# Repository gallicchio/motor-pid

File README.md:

# PID Motor Control Loop PCB

The motor-position feedback loop of *Learning the Art of Electronics* (Hayes &
Horowitz), Lab 10L, as a 170 x 120 mm printed circuit board whose silkscreen *is*
the schematic.  A motorized slide fader (the lab's Bourns PSM01-082A-103B2, or
any 100 mm fader with a 10k track and a 6–11 V motor) wires to two screw terminals; the
board holds the fader's wiper at the position a knob or a signal generator asks
for, with proportional, derivative and integral terms the student switches in
and turns up one at a time, exactly as the lab does.

Every node the lab asks you to look at has a probe loop (17 probe loops, four
of them ground).  Every stage sits in a dashed box named as the book names it.
The three gain trimmers are labelled P GAIN, D GAIN and I GAIN, each with an arc
over it saying what clockwise does (more resistance: more P, more D, less I);
the switches say in words what each position does.

## What is on it

| block | the book | here |
|---|---|---|
| TARGET | a 10k pot between ±15 V through 6.8k | a knob with a centre detent (0 V, clockwise positive), or a BNC jack for a slow square wave; a switch picks |
| pseudo op-amp | unity difference amplifier, inverter, summing amplifier | U1, U2, U3 (LM321) with 100k and 10k as drawn; the summing amplifier's gain is the P GAIN trimmer |
| derivative | C and 1k into an op-amp with 1M feedback, 470 pF across it | U4; a switch picks 22 nF (right for this fader) or the book's 100 nF; D IN / OFF switch |
| integral | 1k + 1M into an op-amp with a capacitor across it | U5 with a 1 µF polypropylene film (its value holds at any voltage); I IN / OFF, where OFF shorts the capacitor so the integrator starts from zero |
| motor driver | op-amp driving a push-pull pair, 10k feedback from the motor side, 0.33 µF from the op-amp's own output, 270 Ω into the bases, 10 Ω + 0.1 µF snubber | U6 with MJB44H11 / MJB45H11 in D2PAK, each in a 2 oz copper pour that is its heatsink, clamp diodes to the rails, a 0.35 A resettable fuse between the push-pull and DRIVE, with red lamps across it: the feedback, the DRIVE loop, DRIVE OUT and the motor are behind it; two more Schottkys clamp a rail left open |
| the plant | the fader's motor and 10k track with 4.7k end resistors (±7.7 V) | two 3-way screw terminals, MOTOR and POT, a POSITION probe loop and a buffered POSITION OUT jack |
| LOOP switch | the book's "break the loop here" | open (POSITION replaced by ground) or closed |

The design departs from the book where the parts or the pedagogy asked for it;
each departure is in [docs/DESIGN_NOTES.md](docs/DESIGN_NOTES.md).

## Using it

[docs/HANDBOOK.md](docs/HANDBOOK.md): bring-up without the fader, wiring the
fader and checking its polarity, the expected voltage at every loop, and the
lab's exercises in the lab's order (P alone and the residual error, raising the
gain until it oscillates, adding D, then I, then driving it with a square
wave).  The back of the board carries the short version.

## Ordering it

[docs/MANUFACTURING.md](docs/MANUFACTURING.md) is generated by the build: the
files to upload, JLCPCB's order form field by field, the cost, and what to look
at in their placement preview.  There are about $12.21 in parts per board.
Order **2 oz** outer copper, not the default 1 oz: the copper round the two
power transistors is their heatsink.

## Building it

```
./make.py
```

runs, from `scripts/parts.py` outward: the footprints and 3D stand-ins, the
ngspice simulation of the loop (from the exported netlist, with a model of the
fader), the schematic (`scripts/gen_sch.py`) and its ERC, 258 circuit
assertions on the netlist (`scripts/check_circuit.py`), the board
(`scripts/layout.py` placed and wired by `scripts/gen_pcb.py`, where every
drawn wire is laid as copper) and its DRC with schematic parity, the fab
package and its checks (`scripts/check_outputs.py`), and the documents, whose
every quoted number is checked against the build.  KiCad 10 is needed; the
build finds its AppImage.

## Files

- `hardware/` — the KiCad project (generated; do not edit by hand)
- `scripts/` — the generators and checkers
- `sim/` — the simulation and its results
- `out/motorpid/` — gerbers, BOM, CPL, prints, assembly notes
- `docs/` — handbook, design notes, manufacturing, images
- `CLAUDE_CODE_CHAT.md` — how this was designed, prompt by prompt

## Licence

Hardware under CERN-OHL-P v2 (`LICENSE-HARDWARE.txt`), scripts under MIT
(`LICENSE`).  The circuit is Hayes & Horowitz's; the board is Jason Gallicchio
and Claude, 2026.

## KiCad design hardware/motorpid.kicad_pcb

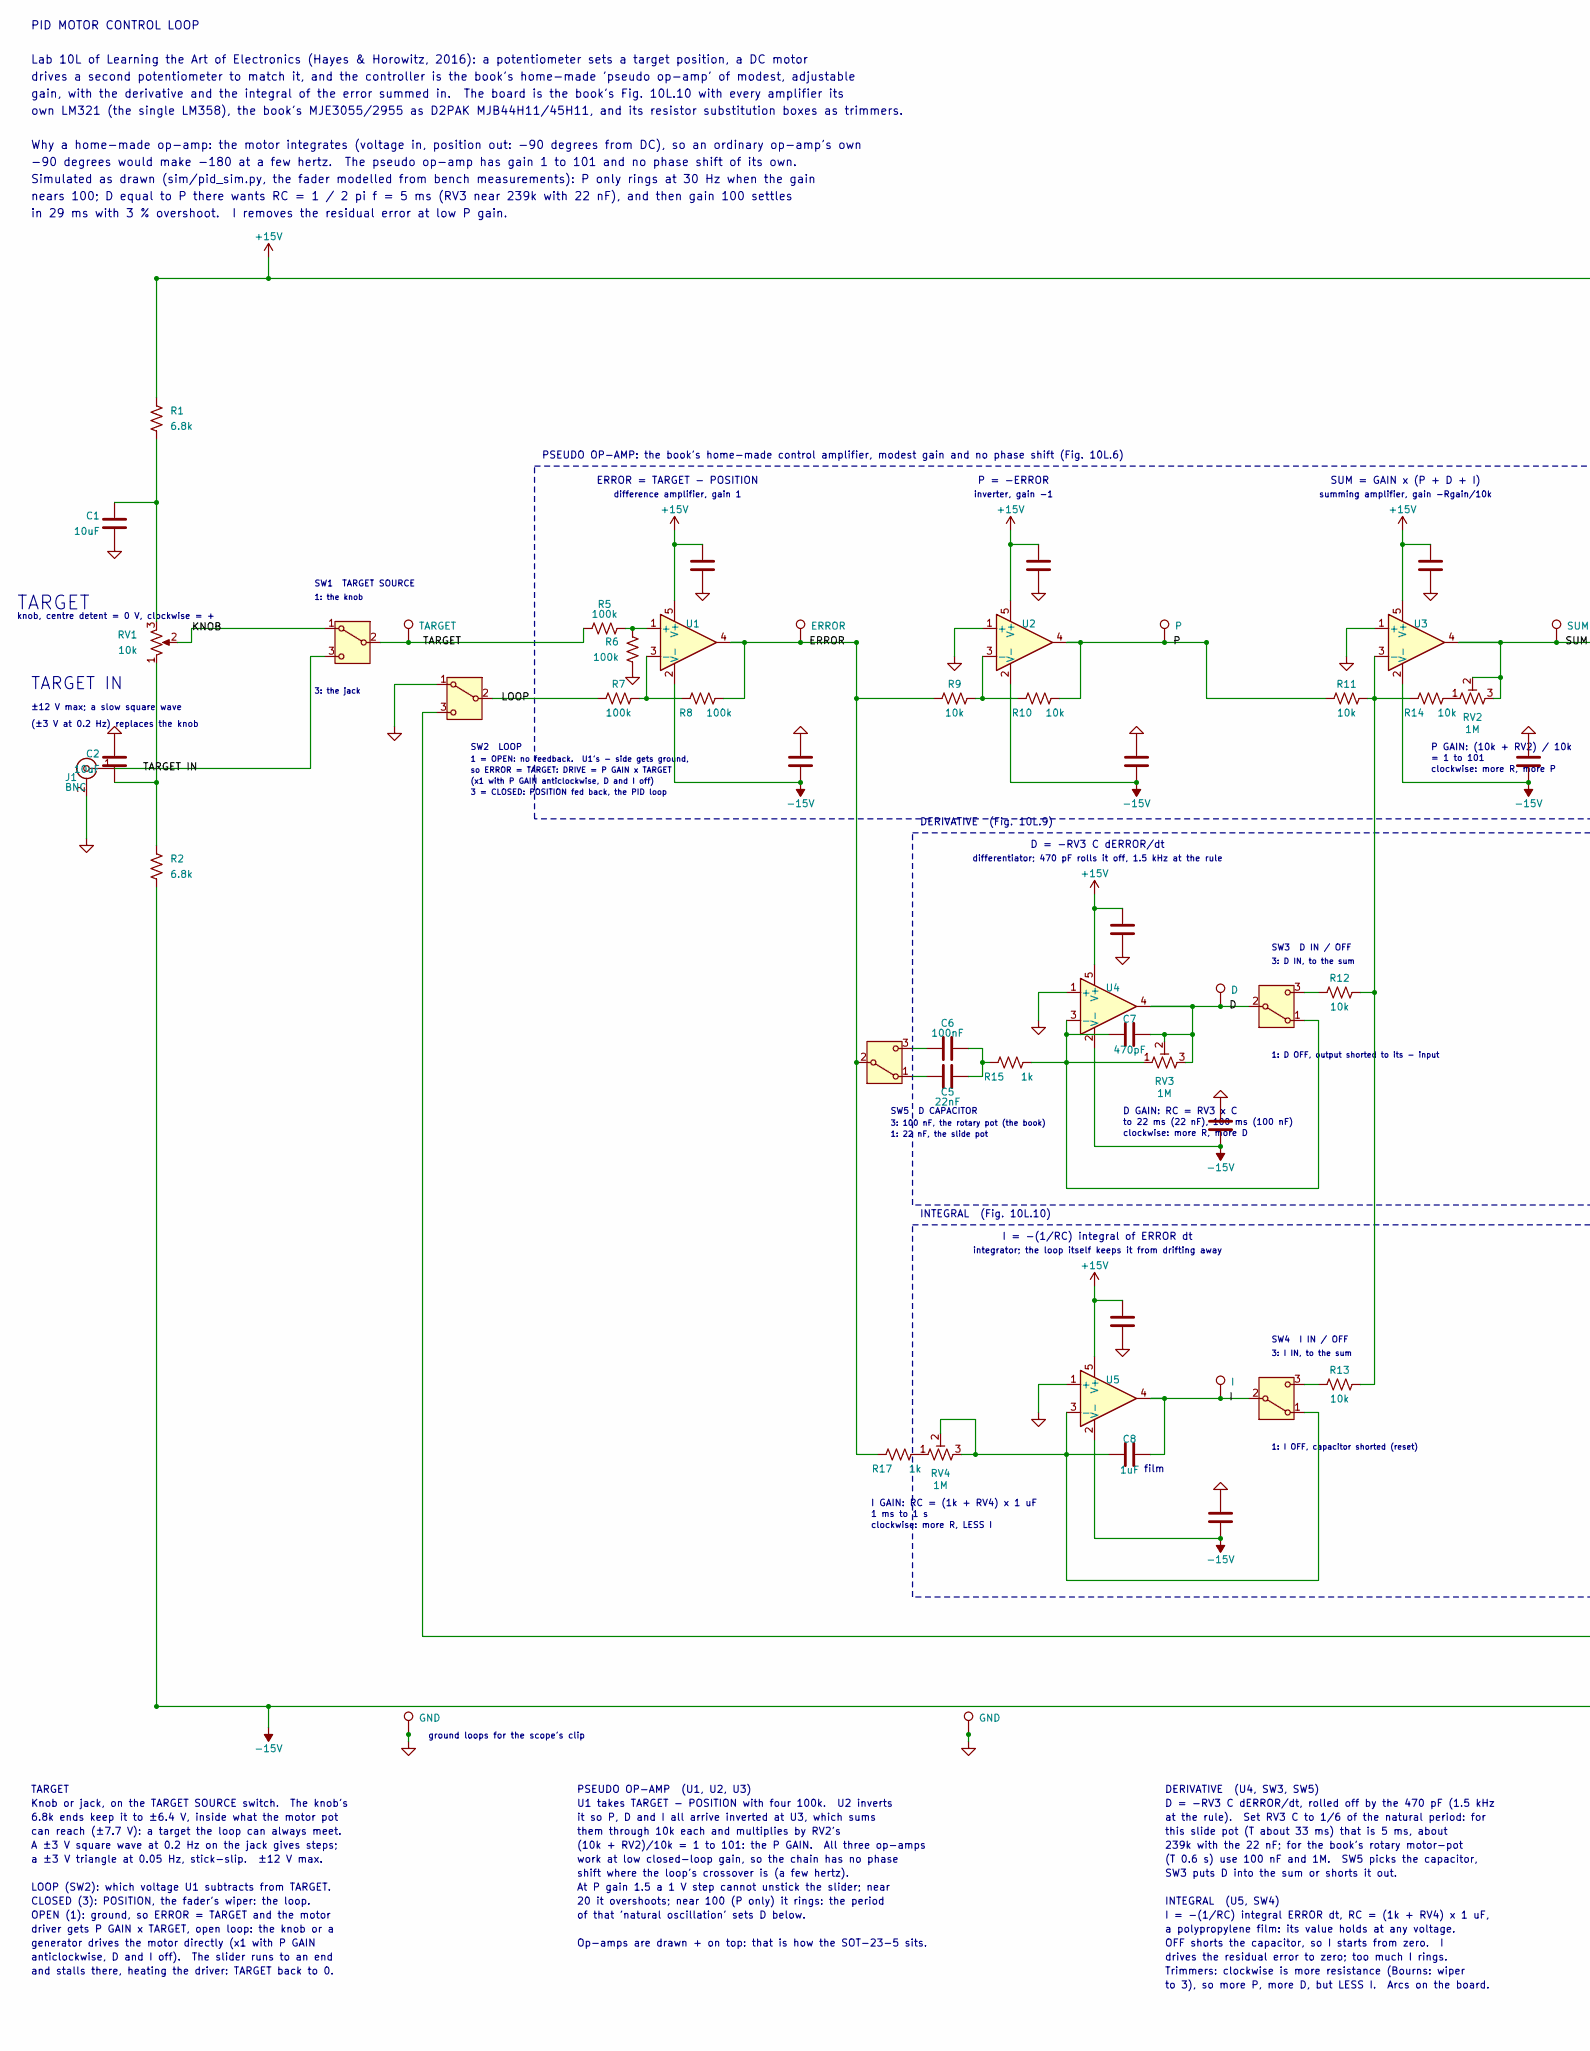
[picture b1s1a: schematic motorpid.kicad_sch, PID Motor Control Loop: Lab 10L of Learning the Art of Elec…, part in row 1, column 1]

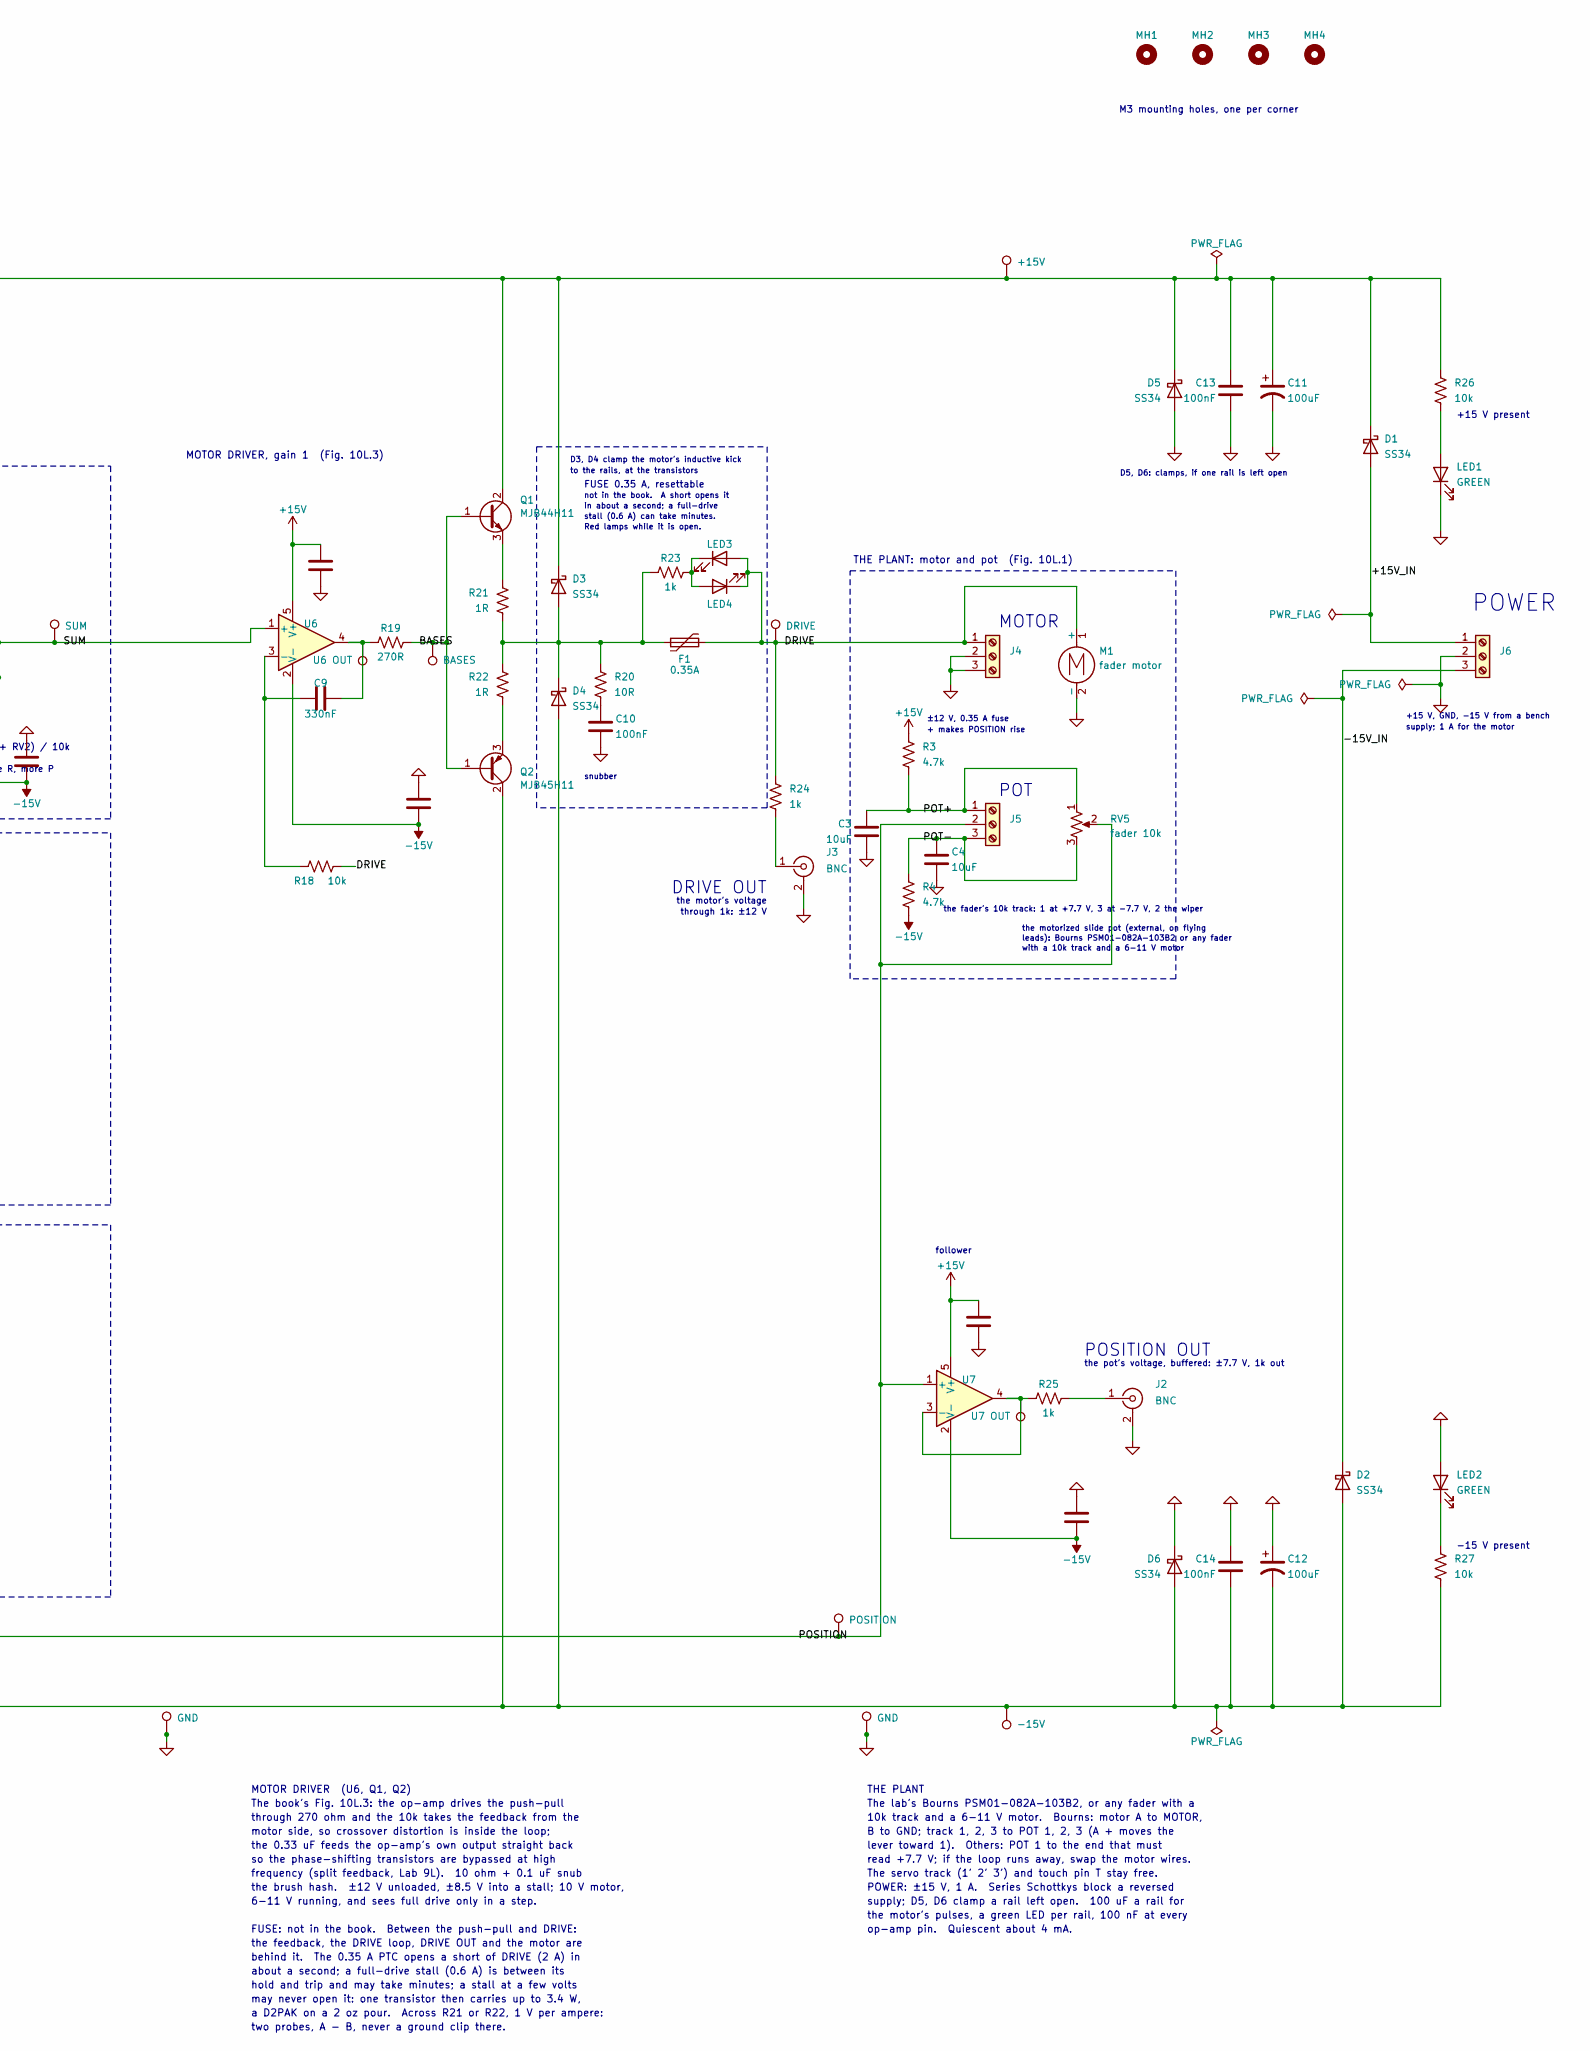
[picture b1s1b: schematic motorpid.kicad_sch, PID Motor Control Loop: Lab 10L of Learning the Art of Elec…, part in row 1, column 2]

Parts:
C1, C2, C3, C4: 10uF; C_0805_2012Metric; MPN CL21A106KAYNNNE; LCSC C15850
C5: 22nF; C_0805_2012Metric; MPN CL21B223KBANNNC; LCSC C1729
C6, C10, C13, C14, C20, C21, C22, C23, C24, C25, C26, C27, C28, C29, C30, C31, C32, C33: 100nF; C_0805_2012Metric; MPN CC0805KRX7R9BB104; LCSC C49678
C7: 470pF; C_0805_2012Metric; MPN 0805B471K500NT; LCSC C1743
C8: 1uF; C_Film_Panasonic_ECWF_L18.1mm_W9.3mm_P15.00mm; MPN ECWF2W105JA; LCSC C242107
C9: 330nF; C_0805_2012Metric; MPN 0805B334K500NT; LCSC C1740
C11, C12: 100uF; CP_Elec_6.3x5.4; MPN JVJ25V100M6x5; LCSC C46550402
D1, D2, D3, D4, D5, D6: SS34; D_SMA; MPN SS34; LCSC C8678
F1: 0.35A; Fuse_1812_4532Metric; MPN 1812L035/60GR; LCSC C18198330
J1, J2, J3: BNC; BNC_KYWE_RightAngle; MPN BNC-KYWE-295-W4-N; LCSC C41416668
J4: MOTOR + - shield; TerminalBlock_KF301_1x03_P5.00mm; MPN KF301-5.0-3P; LCSC C474882
J5: POT 1 (+) 2 (wiper) 3 (-); TerminalBlock_KF301_1x03_P5.00mm; MPN KF301-5.0-3P; LCSC C474882
J6: +15 / GND / -15; TerminalBlock_KF301_1x03_P5.00mm; MPN KF301-5.0-3P; LCSC C474882
LED1, LED2: GREEN; LED_0805_2012Metric; MPN KT-0805G; LCSC C2297
LED3, LED4: RED; LED_0805_2012Metric; MPN NCD0805R1; LCSC C84256
M1: fader motor
MH1, MH2, MH3, MH4: MountingHole; MountingHole_3.2mm_M3
Q1: MJB44H11; TO-263-2; MPN MJB44H11T4G; LCSC C233689
Q2: MJB45H11; TO-263-2; MPN MJB45H11T4G; LCSC C154570
R1, R2: 6.8k; R_0805_2012Metric; MPN 0805W8F6801T5E; LCSC C17772
R3, R4: 4.7k; R_0805_2012Metric; MPN 0805W8F4701T5E; LCSC C17673
R5, R6, R7, R8: 100k; R_0805_2012Metric; MPN 0805W8F1003T5E; LCSC C149504
R9, R10, R11, R12, R13, R14, R18, R26, R27: 10k; R_0805_2012Metric; MPN 0805W8F1002T5E; LCSC C17414
R15, R17, R23: 1k; R_0805_2012Metric; MPN 0805W8F1001T5E; LCSC C17513
R19: 270R; R_0805_2012Metric; MPN 0805W8F2700T5E; LCSC C17590
R20: 10R; R_0805_2012Metric; MPN 0805W8F100JT5E; LCSC C17415
R21, R22: 1R; R_2512_6332Metric; MPN FRC2512J1R0TS; LCSC C3000711
R24, R25: 1k; R_1206_3216Metric; MPN 1206W4F1001T5E; LCSC C4410
RV1: 10k; Potentiometer_Alps_RK09K_Single_Vertical; MPN RK09K1130A70; LCSC C351173
RV2, RV3, RV4: 1M; Potentiometer_Bourns_3362P_Vertical; MPN 3362P-1-105; LCSC C118945
RV5: fader 10k
SW1: TARGET SOURCE; SW_SPDT_Shouhan_MSK12C02; MPN MSK12C02; LCSC C431540
SW2: LOOP; SW_SPDT_Shouhan_MSK12C02; MPN MSK12C02; LCSC C431540
SW3: D IN / OFF; SW_SPDT_Shouhan_MSK12C02; MPN MSK12C02; LCSC C431540
SW4: I IN / OFF; SW_SPDT_Shouhan_MSK12C02; MPN MSK12C02; LCSC C431540
SW5: D CAPACITOR; SW_SPDT_Shouhan_MSK12C02; MPN MSK12C02; LCSC C431540
TP1: TARGET; TestPoint_Loop_RH-5019; MPN RH-5019; LCSC C5199800
TP2: ERROR; TestPoint_Loop_RH-5019; MPN RH-5019; LCSC C5199800
TP3: P; TestPoint_Loop_RH-5019; MPN RH-5019; LCSC C5199800
TP4: D; TestPoint_Loop_RH-5019; MPN RH-5019; LCSC C5199800
TP5: I; TestPoint_Loop_RH-5019; MPN RH-5019; LCSC C5199800
TP6: SUM; TestPoint_Loop_RH-5019; MPN RH-5019; LCSC C5199800
TP7: DRIVE; TestPoint_Loop_RH-5019; MPN RH-5019; LCSC C5199800
TP8: POSITION; TestPoint_Loop_RH-5019; MPN RH-5019; LCSC C5199800
TP9: +15V; TestPoint_Loop_RH-5019; MPN RH-5019; LCSC C5199800
TP10: -15V; TestPoint_Loop_RH-5019; MPN RH-5019; LCSC C5199800
TP11: BASES; TestPoint_Loop_RH-5019; MPN RH-5019; LCSC C5199800
TP12: U6 OUT; TestPoint_Loop_RH-5019; MPN RH-5019; LCSC C5199800
TP13: U7 OUT; TestPoint_Loop_RH-5019; MPN RH-5019; LCSC C5199800
TP100, TP101, TP102, TP103: GND; TestPoint_Loop_RH-5019; MPN RH-5019; LCSC C5199800
U1, U2, U3, U4, U5, U6, U7: LM321; SOT-23-5; MPN LM321MFX/NOPB; LCSC C9405

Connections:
+15V: C11.1, C13.1, C20.1, C22.1, C24.1, C26.1, C28.1, C30.1, C32.1, D1.1 (K), D3.1 (K), D5.1 (K), Q1.2 (C), R1.1, R3.1, R26.1, TP9.1, U1.5 (V+), U2.5 (V+), U3.5 (V+), U4.5 (V+), U5.5 (V+), U6.5 (V+), U7.5 (V+)
-15V: C12.2, C14.2, C21.2, C23.2, C25.2, C27.2, C29.2, C31.2, C33.2, D2.2 (A), D4.2 (A), D6.2 (A), Q2.2 (C), R2.2, R4.2, R27.2, TP10.1, U1.2 (V-), U2.2 (V-), U3.2 (V-), U4.2 (V-), U5.2 (V-), U6.2 (V-), U7.2 (V-)
/+15V_IN: D1.2 (A), J6.1
/-15V_IN: D2.1 (K), J6.3
/BASES: Q1.1 (B), Q2.1 (B), R19.2, TP11.1
/D: C7.2, RV3.2, RV3.3, SW3.2 (B), TP4.1, U4.4
/DRIVE: F1.2, J4.1, LED3.2 (A), LED4.1 (K), M1.1 (+), R18.2, R24.1, TP7.1
/ERROR: R8.2, R9.1, R17.1, SW5.2 (B), TP2.1, U1.4
/I: C8.2, SW4.2 (B), TP5.1, U5.4
/KNOB: RV1.2, SW1.1 (A)
/LOOP: R7.1, SW2.2 (B)
/P: R10.2, R11.1, TP3.1, U2.4
/POSITION: J5.2, RV5.2, SW2.3 (C), TP8.1, U7.1 (+)
/POT+: C3.1, J5.1, R3.2, RV5.1
/POT-: C4.1, J5.3, R4.1, RV5.3
/SUM: RV2.2, RV2.3, TP6.1, U3.4, U6.1 (+)
/TARGET: R5.1, SW1.2 (B), TP1.1
/TARGET IN: J1.1 (In), SW1.3 (C)
GND: C1.2, C2.1, C3.2, C4.2, C10.2, C11.2, C12.1, C13.2, C14.1, C20.2, C21.1, C22.2, C23.1, C24.2, C25.1, C26.2, C27.1, C28.2, C29.1, C30.2, C31.1, C32.2, C33.1, D5.2 (A), D6.1 (K), J1.2 (Ext), J2.2 (Ext), J3.2 (Ext), J4.2, J4.3, J6.2, LED1.1 (K), LED2.2 (A), M1.2 (-), R6.2, SW2.1 (A), TP100.1, TP101.1, TP102.1, TP103.1, U2.1 (+), U3.1 (+), U4.1 (+), U5.1 (+)
unnamed: C1.1, R1.2, RV1.3
unnamed: C2.2, R2.1, RV1.1
unnamed: C5.2, C6.2, R15.1
unnamed: C9.2, R19.1, TP12.1, U6.4
unnamed: C10.1, R20.2
unnamed: D3.2 (A), D4.1 (K), F1.1, R20.1, R21.2, R22.1, R23.1
unnamed: J2.1 (In), R25.2
unnamed: J3.1 (In), R24.2
unnamed: LED1.2 (A), R26.2
unnamed: LED2.1 (K), R27.1
unnamed: LED3.1 (K), LED4.2 (A), R23.2
unnamed: Q1.3 (E), R21.1
unnamed: Q2.3 (E), R22.2
unnamed: R14.2, RV2.1
unnamed: R17.2, RV4.1
unnamed: C7.1, R15.2, RV3.1, SW3.1 (A), U4.3 (-)
unnamed: R12.1, SW3.3 (C)
unnamed: C8.1, RV4.2, RV4.3, SW4.1 (A), U5.3 (-)
unnamed: R13.1, SW4.3 (C)
unnamed: C5.1, SW5.1 (A)
unnamed: C6.1, SW5.3 (C)
unnamed: R5.2, R6.1, U1.1 (+)
unnamed: R7.2, R8.1, U1.3 (-)
unnamed: R9.2, R10.1, U2.3 (-)
unnamed: R11.2, R12.2, R13.2, R14.1, U3.3 (-)
unnamed: C9.1, R18.1, U6.3 (-)
unnamed: R25.1, TP13.1, U7.3 (-), U7.4

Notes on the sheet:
POWER: ±15 V, 1 A. Series Schottkys block a reversed
the motor's pulses, a green LED per rail, 100 nF at every
6.8k ends keep it to ±6.4 V, inside what the motor pot
film
this slide pot (T about 33 ms) that is 5 ms, about
anticlockwise, D and I off). The slider runs to an end
it so P, D and I all arrive inverted at U3, which sums
B to GND; track 1, 2, 3 to POT 1, 2, 3 (A + moves the
motor side, so crossover distortion is inside the loop;
the feedback, the DRIVE loop, DRIVE OUT and the motor are
ground loops for the scope's clip
1: 22 nF, the slide pot
drives the residual error to zero; too much I rings.
PSEUDO OP-AMP (U1, U2, U3)
SW2 LOOP
10k track and a 6-11 V motor. Bourns: motor A to MOTOR,
with a 10k track and a 6-11 V motor
The servo track (1' 2' 3') and touch pin T stay free.
= 1 to 101
I GAIN: RC = (1k + RV4) x 1 uF
PSEUDO OP-AMP: the book's home-made control amplifier, modest gain and no phase shift (Fig. 10L.6)
THE PLANT
239k with the 22 nF; for the book's rotary motor-pot
difference amplifier, gain 1
two probes, A - B, never a ground clip there.
in 29 ms with 3 % overshoot. I removes the residual error at low P gain.
+15 V present
SW5 D CAPACITOR
D5, D6: clamps, if one rail is left open
FUSE 0.35 A, resettable
3: D IN, to the sum
snubber
POSITION OUT
driver gets P GAIN x TARGET, open loop: the knob or a
Trimmers: clockwise is more resistance (Bourns: wiper
M3 mounting holes, one per corner
DERIVATIVE (Fig. 10L.9)
inverter, gain -1
them through 10k each and multiplies by RV2's
OFF shorts the capacitor, so I starts from zero. I

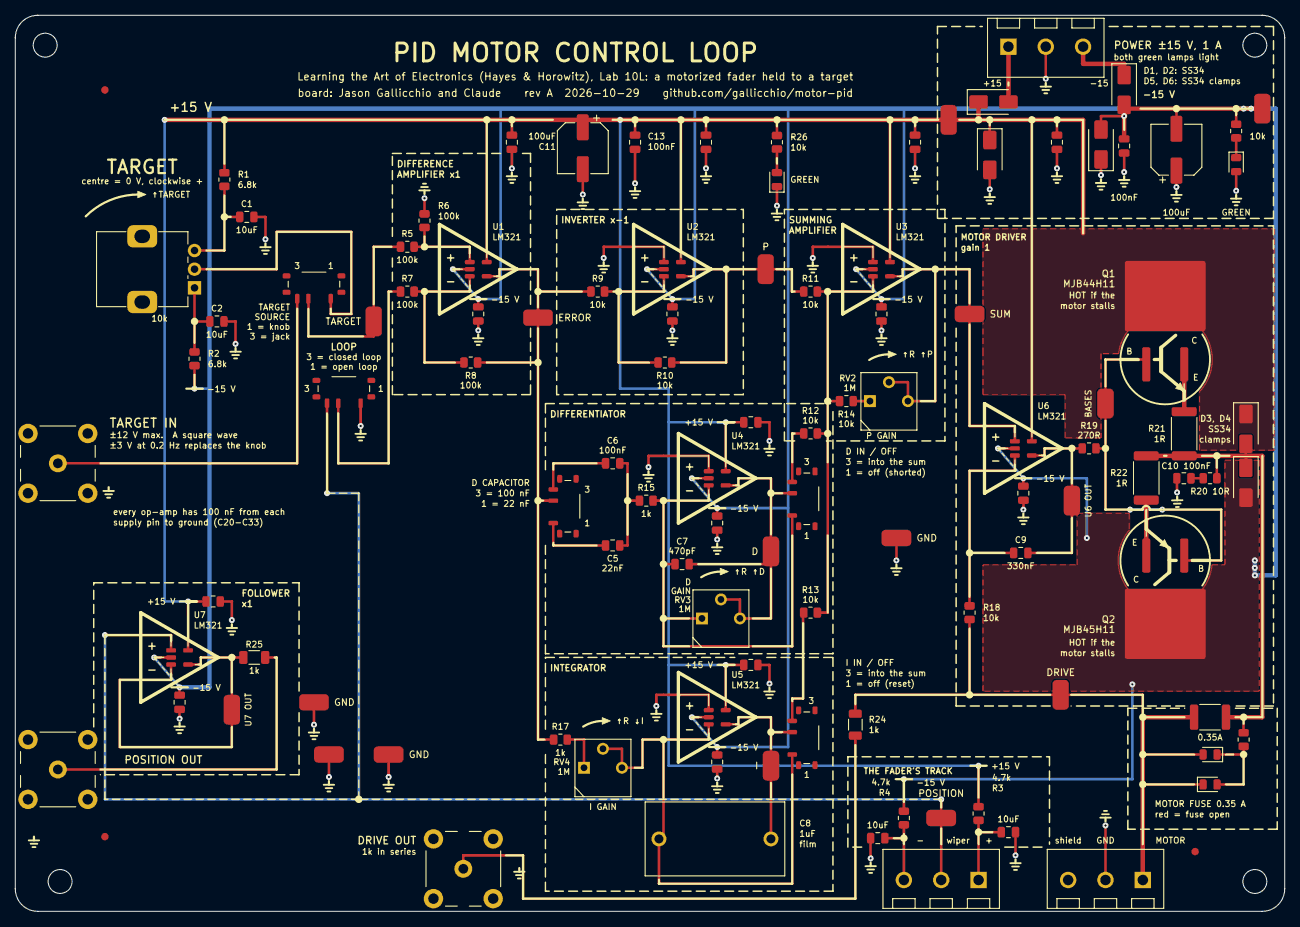
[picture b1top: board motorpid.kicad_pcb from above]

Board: 2 copper layers, 170.0 x 120.0 mm, 110 parts (0 on the bottom side), 46 nets.

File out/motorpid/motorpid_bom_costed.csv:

Comment,Designator,Footprint,LCSC Part #,MPN,Qty,Unit $,Ext $,JLC
22nF,C5,C_0805_2012Metric,C1729,CL21B223KBANNNC,1,0.0084,0.008,basic
470pF,C7,C_0805_2012Metric,C1743,0805B471K500NT,1,0.0075,0.007,basic
1uF,C8,C_Film_Panasonic_ECWF_L18.1mm_W9.3mm_P15.00mm,C242107,ECWF2W105JA,1,0.3259,0.326,extended
330nF,C9,C_0805_2012Metric,C1740,0805B334K500NT,1,0.0207,0.021,preferred
100uF,"C11,C12",CP_Elec_6.3x5.4,C46550402,JVJ25V100M6x5,2,0.0423,0.085,extended
10uF,"C1,C2,C3,C4",C_0805_2012Metric,C15850,CL21A106KAYNNNE,4,0.0426,0.170,basic
100nF,"C6,C10,C13,C14,C20,C21,C22,C23,C24,C25,C26,C27,C28,C29,C30,C31,C32,C33",C_0805_2012Metric,C49678,CC0805KRX7R9BB104,18,0.0205,0.369,basic
SS34,"D1,D2,D3,D4,D5,D6",D_SMA,C8678,SS34,6,0.0351,0.211,basic
0.35A,F1,Fuse_1812_4532Metric,C18198330,1812L035/60GR,1,0.0667,0.067,extended
MOTOR + - shield,J4,TerminalBlock_KF301_1x03_P5.00mm,C474882,KF301-5.0-3P,1,0.1396,0.140,extended
POT 1 (+) 2 (wiper) 3 (-),J5,TerminalBlock_KF301_1x03_P5.00mm,C474882,KF301-5.0-3P,1,0.1396,0.140,extended
+15 / GND / -15,J6,TerminalBlock_KF301_1x03_P5.00mm,C474882,KF301-5.0-3P,1,0.1396,0.140,extended
BNC,"J1,J2,J3",BNC_KYWE_RightAngle,C41416668,BNC-KYWE-295-W4-N,3,1.2929,3.879,extended
GREEN,"LED1,LED2",LED_0805_2012Metric,C2297,KT-0805G,2,0.0164,0.033,basic
RED,"LED3,LED4",LED_0805_2012Metric,C84256,NCD0805R1,2,0.0135,0.027,basic
MJB44H11,Q1,TO-263-2,C233689,MJB44H11T4G,1,1.2244,1.224,extended
MJB45H11,Q2,TO-263-2,C154570,MJB45H11T4G,1,1.1573,1.157,extended
270R,R19,R_0805_2012Metric,C17590,0805W8F2700T5E,1,0.0070,0.007,preferred
10R,R20,R_0805_2012Metric,C17415,0805W8F100JT5E,1,0.0040,0.004,basic
10k,RV1,Potentiometer_Alps_RK09K_Single_Vertical,C351173,RK09K1130A70,1,0.5335,0.533,extended
6.8k,"R1,R2",R_0805_2012Metric,C17772,0805W8F6801T5E,2,0.0029,0.006,basic
4.7k,"R3,R4",R_0805_2012Metric,C17673,0805W8F4701T5E,2,0.0051,0.010,basic
1R,"R21,R22",R_2512_6332Metric,C3000711,FRC2512J1R0TS,2,0.0313,0.063,extended
1k,"R24,R25",R_1206_3216Metric,C4410,1206W4F1001T5E,2,0.0085,0.017,basic
1k,"R15,R17,R23",R_0805_2012Metric,C17513,0805W8F1001T5E,3,0.0035,0.011,basic
100k,"R5,R6,R7,R8",R_0805_2012Metric,C149504,0805W8F1003T5E,4,0.0059,0.024,basic
1M,"RV2,RV3,RV4",Potentiometer_Bourns_3362P_Vertical,C118945,3362P-1-105,3,0.1585,0.476,extended
10k,"R9,R10,R11,R12,R13,R14,R18,R26,R27",R_0805_2012Metric,C17414,0805W8F1002T5E,9,0.0034,0.031,basic
TARGET SOURCE,SW1,SW_SPDT_Shouhan_MSK12C02,C431540,MSK12C02,1,0.0544,0.054,extended
LOOP,SW2,SW_SPDT_Shouhan_MSK12C02,C431540,MSK12C02,1,0.0544,0.054,extended
D IN / OFF,SW3,SW_SPDT_Shouhan_MSK12C02,C431540,MSK12C02,1,0.0544,0.054,extended
I IN / OFF,SW4,SW_SPDT_Shouhan_MSK12C02,C431540,MSK12C02,1,0.0544,0.054,extended
D CAPACITOR,SW5,SW_SPDT_Shouhan_MSK12C02,C431540,MSK12C02,1,0.0544,0.054,extended
TARGET,TP1,TestPoint_Loop_RH-5019,C5199800,RH-5019,1,0.0966,0.097,extended
ERROR,TP2,TestPoint_Loop_RH-5019,C5199800,RH-5019,1,0.0966,0.097,extended
P,TP3,TestPoint_Loop_RH-5019,C5199800,RH-5019,1,0.0966,0.097,extended
D,TP4,TestPoint_Loop_RH-5019,C5199800,RH-5019,1,0.0966,0.097,extended
I,TP5,TestPoint_Loop_RH-5019,C5199800,RH-5019,1,0.0966,0.097,extended
SUM,TP6,TestPoint_Loop_RH-5019,C5199800,RH-5019,1,0.0966,0.097,extended
DRIVE,TP7,TestPoint_Loop_RH-5019,C5199800,RH-5019,1,0.0966,0.097,extended
POSITION,TP8,TestPoint_Loop_RH-5019,C5199800,RH-5019,1,0.0966,0.097,extended
+15V,TP9,TestPoint_Loop_RH-5019,C5199800,RH-5019,1,0.0966,0.097,extended
-15V,TP10,TestPoint_Loop_RH-5019,C5199800,RH-5019,1,0.0966,0.097,extended
BASES,TP11,TestPoint_Loop_RH-5019,C5199800,RH-5019,1,0.0966,0.097,extended
U6 OUT,TP12,TestPoint_Loop_RH-5019,C5199800,RH-5019,1,0.0966,0.097,extended
U7 OUT,TP13,TestPoint_Loop_RH-5019,C5199800,RH-5019,1,0.0966,0.097,extended
GND,"TP100,TP101,TP102,TP103",TestPoint_Loop_RH-5019,C5199800,RH-5019,4,0.0966,0.386,extended
LM321,"U1,U2,U3,U4,U5,U6,U7",SOT-23-5,C9405,LM321MFX/NOPB,7,0.1578,1.105,extended

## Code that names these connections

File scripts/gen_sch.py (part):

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    SW1_X = g(36)
    w1, w2, w3 = switch("SW1", "TARGET SOURCE", SW1_X, A_Y, "y", "1: the knob", "3: the jack")
    s.wire(k2, (k2[0] + 2.54, k2[1]), (k2[0] + 2.54, w1[1]), w1)
    label("KNOB", k2[0] + 2.54, w1[1], justify="left")
    JX = KX - 12.7                                    # left of the knob's own column
    s.place("Connector:Conn_Coaxial", "J1", "BNC", JX, g(60) + 2.54, mirror="y",
            footprint=fp("BNC"), fields=part_fields("BNC"),
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    s.text("TARGET IN", g(13), g(55.0), size=2.2)
    s.text("±12 V max; a slow square wave", g(13), g(56.7), size=1.1)
    s.text("(±3 V at 0.2 Hz) replaces the knob", g(13), g(57.9), size=1.1)
    label("TARGET IN", j1[0] + 5.08, j1[1], justify="left")
    # the switched target, then on to the difference amplifier
    TX = w2[0] + 5.08
    s.wire(w2, (TX, w2[1]))
    testpoint(TX, A_Y, "TARGET", rot=0)
    label("TARGET", TX + 2.54, A_Y)

    # ========================================================= pseudo op-amp ==
    # U1: the unity-gain difference amplifier, "Error".  Target into +, position into -.
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    s.text("clockwise: more R, more P", U3_X + 2.54, n3[1] + 13.0, size=1.1)
    s.wire(o3, (g(126), A_Y))
    testpoint(g(122), A_Y, "SUM", rot=0)
    label("SUM", g(122) + 1.5, A_Y)
    s.text("SUM = GAIN x (P + D + I)", U3_X - 2.0, A_Y - 29.21, size=1.3, justify=None)
    s.text("summing amplifier, gain -Rgain/10k", U3_X - 2.0, A_Y - 26.67, size=1.1, justify=None)
    # the box round the three: the book's "home-made pseudo op-amp"
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    s.wire(o6, (o6[0] + 3.81, o6[1]))
    BX = o6[0] + 17.78                                  # the bases' column
    s.wire((o6[0] + 11.43, o6[1]), (BX, o6[1]))
    label("BASES", o6[0] + 12.7, o6[1])
    testpoint(o6[0] + 15.24, o6[1], "BASES", rot=180, dy=3.2)
    testpoint(c, o6[1], "U6 OUT", rot=180, dx=-1.8, dy=3.2, justify="right")
    # the push-pull: NPN above, PNP below, 1 ohm in each emitter, joined at DRIVE
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    s.wire((OX, A_Y - 3.81), (OX, A_Y + 3.81))
    s.wire((OX, A_Y + 11.43), q2e)
    s.junction(OX, A_Y)
    # the DC feedback comes from DRIVE, behind the fuse: a label, not a wire
    # under the clamps and the fuse
    s.wire((U6_X + 6.35, DCY), (U6_X + 8.89, DCY))
    label("DRIVE", U6_X + 8.89, DCY)
    s.text("MOTOR DRIVER, gain 1  (Fig. 10L.3)", U6_X - 22.0, A_Y - 33.8, size=1.3)
    # --- clamps to the rails and the book's snubber at the transistors, then
    # the fuse with its lamp.  The node between the emitter resistors and the
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    DOX = FX + 16.51                                    # DRIVE: its loop, then DRIVE OUT below
    s.wire((FX + 3.81, A_Y), (DOX, A_Y))
    testpoint(DOX, A_Y, "DRIVE", rot=0)
    label("DRIVE", DOX + 1.5, A_Y)
    # the tripped lamp: two red LEDs anti-parallel with 1k, across the fuse
    LY = A_Y - 12.7
    TL, TR = FX - 7.62, FX + 13.97
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    s.wire(jp2, (POSX, jp2[1]), (POSX, FB_Y), (g(44), FB_Y))
    s.wire(f2, (f2[0] + 2.54, f2[1]), (f2[0] + 2.54, JP_Y + 25.4), (POSX, JP_Y + 25.4))
    s.junction(POSX, JP_Y + 25.4)
    label("POSITION", POSX - 15.0, FB_Y)
    testpoint(POSX - 7.62, FB_Y, "POSITION", rot=0)
    s.text("the motorized slide pot (external, on flying", MX - 10.0, JP_Y + 19.0, size=1.0)
    s.text("leads): Bourns PSM01-082A-103B2 or any fader", MX - 10.0, JP_Y + 20.8, size=1.0)
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    s.wire((g(44), FB_Y), (c3_[0] - 2.54, FB_Y), (c3_[0] - 2.54, c3_[1]), c3_)
    s.wire(c1_, (c1_[0] - 7.62, c1_[1]), (c1_[0] - 7.62, c1_[1] + 7.62))
    gnd(c1_[0] - 7.62, c1_[1] + 7.62)
    label("LOOP", c2_[0] + 1.5, c2_[1])

    # ========================================================== rails ========
    PR = g(221)
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

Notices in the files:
hardware/motorpid.kicad_sch:
Open source, CERN-OHL-P-2.0 -- github.com/gallicchio/motor-pid
scripts/gen_sch.py:
"Open source, CERN-OHL-P-2.0 -- " + parts.PROJECT_URL])
